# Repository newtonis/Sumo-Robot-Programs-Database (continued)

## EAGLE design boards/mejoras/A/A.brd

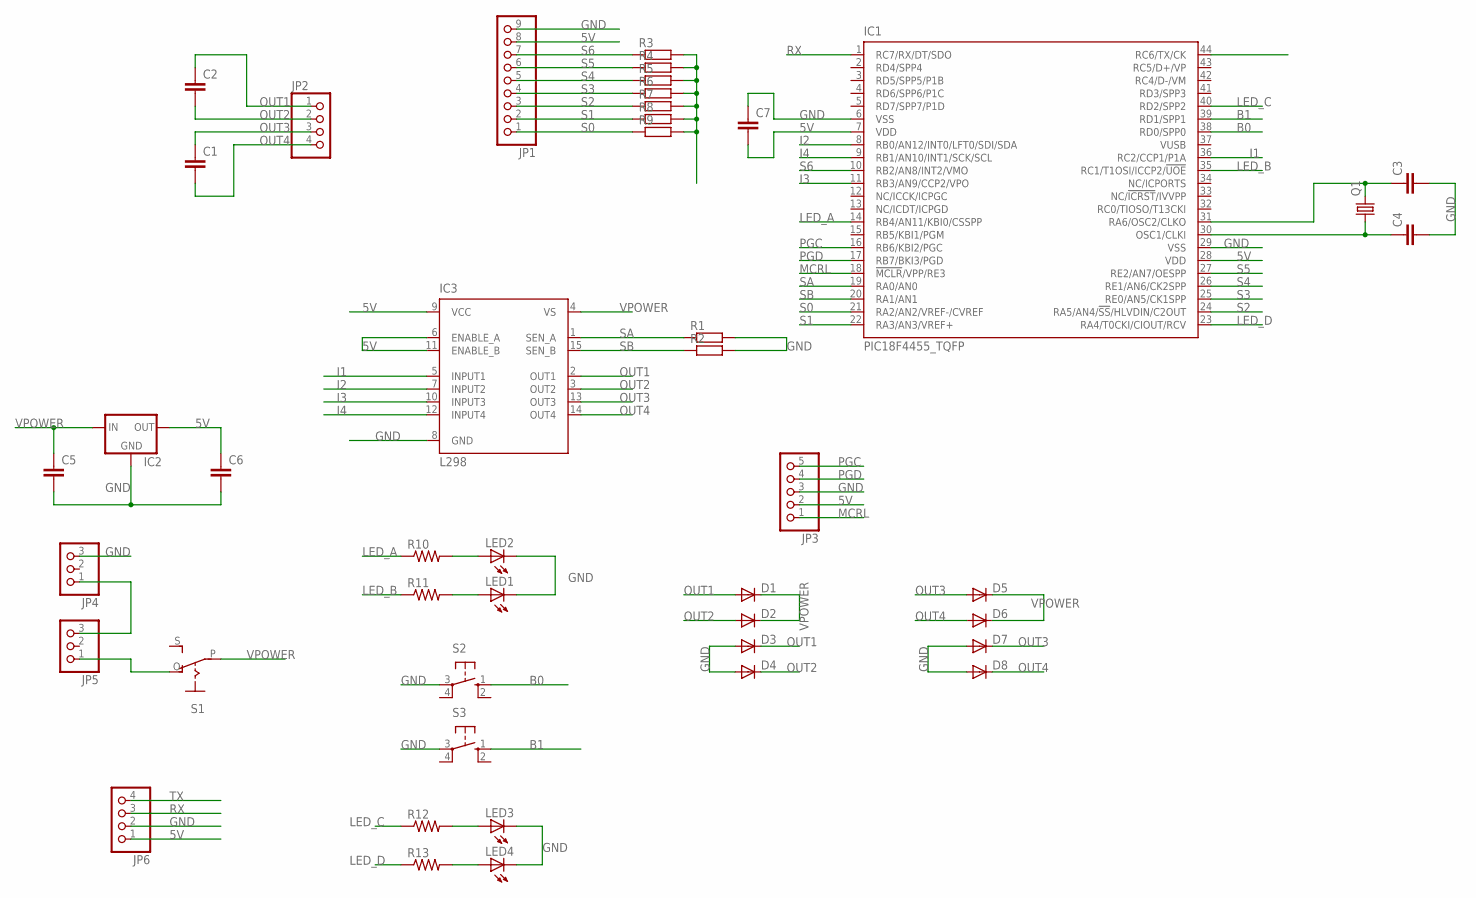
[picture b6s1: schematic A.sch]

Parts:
C1, C2, C3, C4, C5, C6, C7: C2,5-3; C2.5-3
D1, D2, D3, D4, D5, D6, D7, D8: DIODE-DO214AC; DO214AC
IC1: PIC18F4455_TQFP; TQFP44
IC2: 78XXS
IC3: L298; MULTIWATT-15
JP1: PINHD-1X9; 1X09
JP2, JP6: PINHD-1X4; 1X04
JP3: PINHD-1X5; 1X05
JP4, JP5: PINHD-1X3; 1X03
LED1, LED2, LED3, LED4: LEDCHIPLED_1206; CHIPLED_1206
Q1: CRYSTALHC49S; HC49/S
R1, R2: R-EU_R2512; R2512
R3, R4, R5, R6, R7, R8, R9: R-EU_M0805; M0805
R10, R11: R-US_M0805; M0805
R12, R13: R-US_R0805; R0805
S1: EG1218S; EG1218
S2, S3: 10-XX; B3F-10XX

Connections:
5V: C6.1, C7.2, IC1.7 (VDD), IC1.28 (VDD), IC2.OUT, IC3.6 (ENABLE_A), IC3.9 (VCC), IC3.11 (ENABLE_B), JP1.8, JP3.2, JP6.1, R3.2, R4.2, R5.2, R6.2, R7.2, R8.2, R9.2
B0: IC1.38 (RD0/SPP0), S2.1 (S)
B1: IC1.39 (RD1/SPP1), S3.1 (S)
GND: C3.2, C4.2, C5.2, C6.2, C7.1, D3.A, D4.A, D7.A, D8.A, IC1.6 (VSS), IC1.29 (VSS), IC2.GND, IC3.8 (GND), JP1.9, JP3.3, JP4.3, JP6.2, LED1.C, LED2.C, LED3.C, LED4.C, R1.2, R2.2, S2.3, S3.3
I1: IC1.36 (RC2/CCP1/P1A), IC3.5 (INPUT1)
I2: IC1.8 (RB0/AN12/INT0/LFT0/SDI/SDA), IC3.7 (INPUT2)
I3: IC1.11 (RB3/AN9/CCP2/VPO), IC3.10 (INPUT3)
I4: IC1.9 (RB1/AN10/INT1/SCK/SCL), IC3.12 (INPUT4)
LED_A: IC1.14 (RB4/AN11/KBI0/CSSPP), R10.1
LED_B: IC1.35 (RC1/T1OSI/ICCP2/!UOE), R11.1
LED_C: IC1.40 (RD2/SPP2), R12.1
LED_D: IC1.23 (RA4/T0CKI/CIOUT/RCV), R13.1
MCRL: IC1.18 (!MCLR!/VPP/RE3), JP3.1
unnamed: C4.1, IC1.30 (OSC1/CLKI), Q1.1
unnamed: C3.1, IC1.31 (RA6/OSC2/CLKO), Q1.2
unnamed: JP4.1, JP5.3
unnamed: LED2.A, R10.2
unnamed: LED1.A, R11.2
unnamed: LED3.A, R12.2
unnamed: LED4.A, R13.2
OUT1: C2.1, D1.A, D3.C, IC3.2 (OUT1), JP2.1
OUT2: C2.2, D2.A, D4.C, IC3.3 (OUT2), JP2.2
OUT3: C1.1, D5.A, D7.C, IC3.13 (OUT3), JP2.3
OUT4: C1.2, D6.A, D8.C, IC3.14 (OUT4), JP2.4
PGC: IC1.16 (RB6/KBI2/PGC), JP3.5
PGD: IC1.17 (RB7/BKI3/PGD), JP3.4
RX: IC1.1 (RC7/RX/DT/SDO), JP6.3
S0: IC1.21 (RA2/AN2/VREF-/CVREF), JP1.1, R9.1
S1: IC1.22 (RA3/AN3/VREF+), JP1.2, R8.1
S2: IC1.24 (RA5/AN4/!SS!/HLVDIN/C2OUT), JP1.3, R7.1
S3: IC1.25 (RE0/AN5/CK1SPP), JP1.4, R6.1
S4: IC1.26 (RE1/AN6/CK2SPP), JP1.5, R5.1
S5: IC1.27 (RE2/AN7/OESPP), JP1.6, R4.1
S6: IC1.10 (RB2/AN8/INT2/VMO), JP1.7, R3.1
SA: IC1.19 (RA0/AN0), IC3.1 (SEN_A), R1.1
SB: IC1.20 (RA1/AN1), IC3.15 (SEN_B), R2.1
TX: IC1.44 (RC6/TX/CK), JP6.4
VPOWER: C5.1, D1.C, D2.C, D5.C, D6.C, IC2.IN, IC3.4 (VS), S1.P
VPREV: JP5.1, S1.O

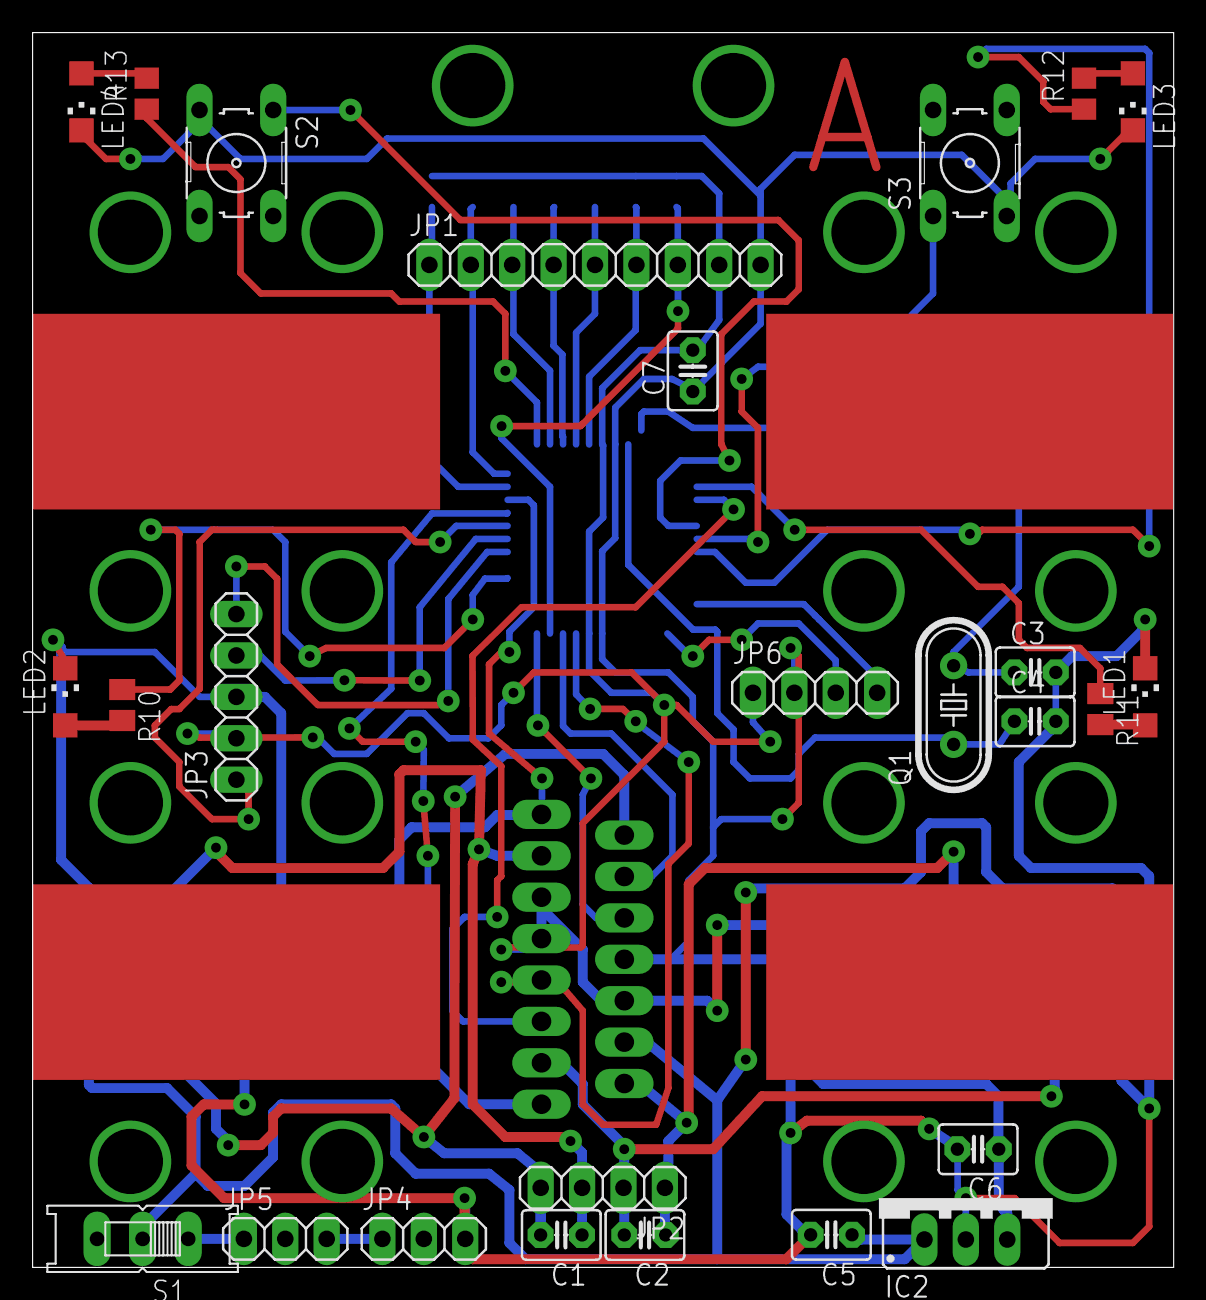
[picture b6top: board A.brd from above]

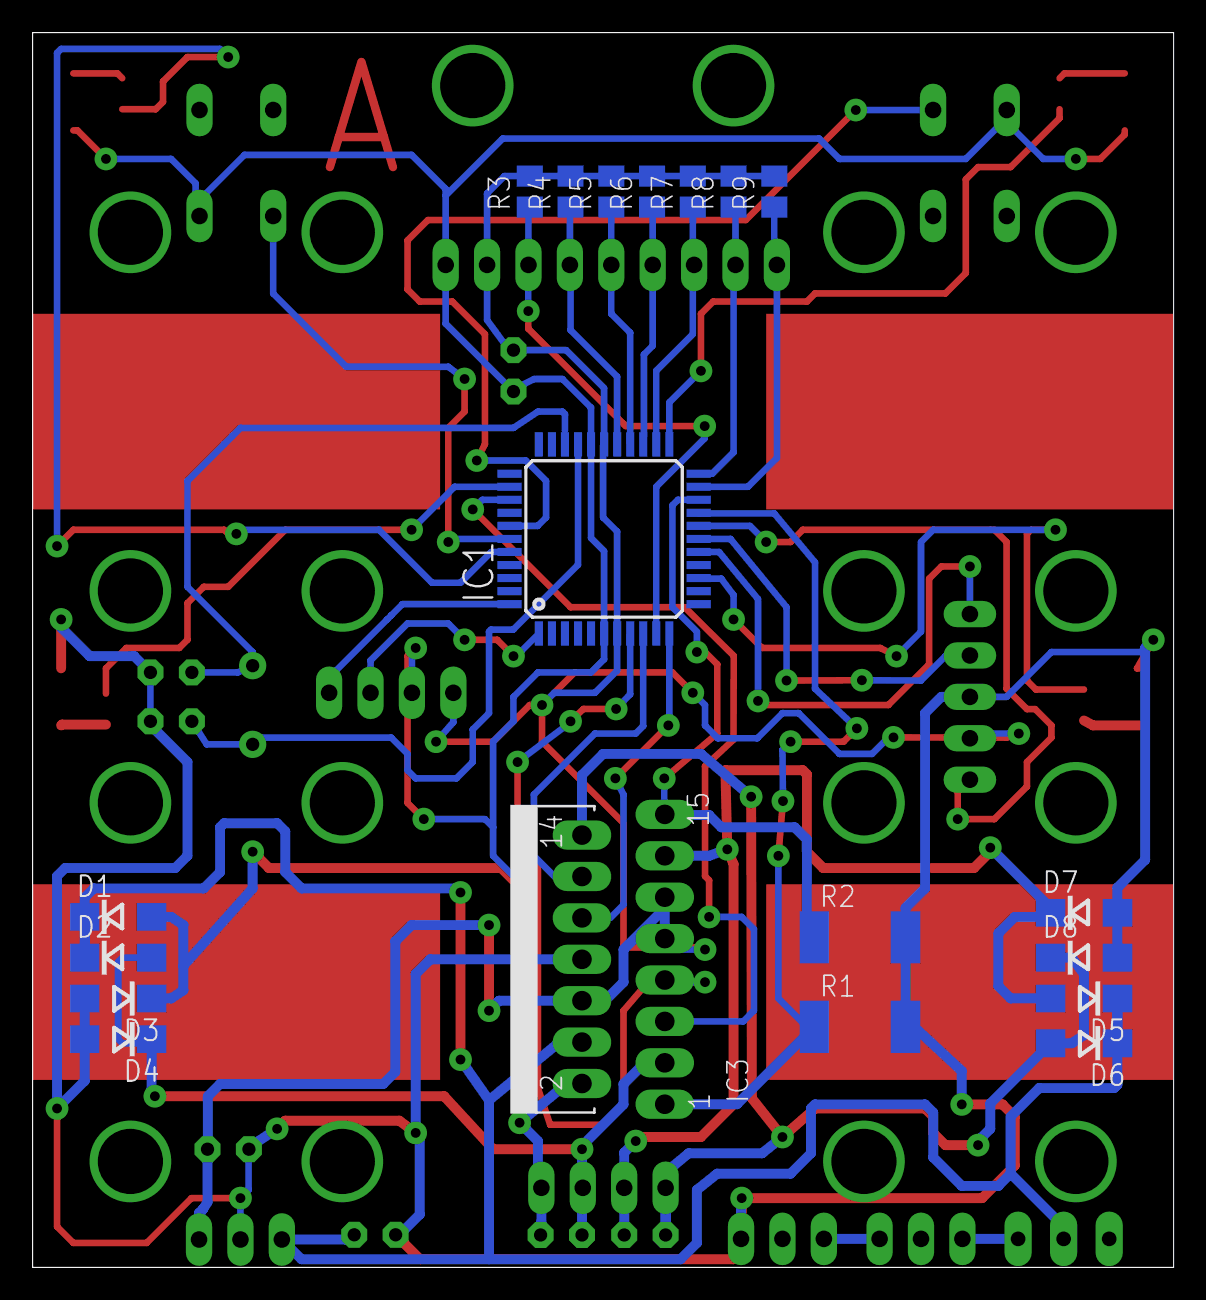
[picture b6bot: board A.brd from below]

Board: 2 copper layers, 70.0 x 75.8 mm, 45 parts (19 on the bottom side), 39 nets.

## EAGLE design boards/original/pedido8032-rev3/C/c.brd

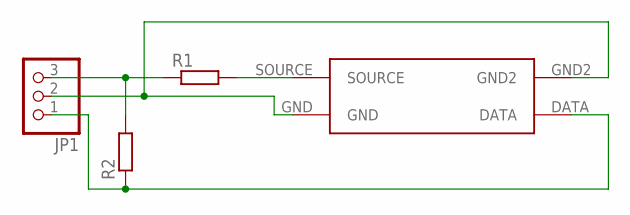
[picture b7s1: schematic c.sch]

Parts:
JP1: PINHD-1X3; 1X03
R1, R2: R-EU_M1206; M1206
U$1: GP2S24

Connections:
unnamed: JP1.3, R1.1, R2.2
unnamed: R1.2, U$1.SOURCE
unnamed: JP1.2, U$1.GND, U$1.GND2
unnamed: JP1.1, R2.1, U$1.DATA

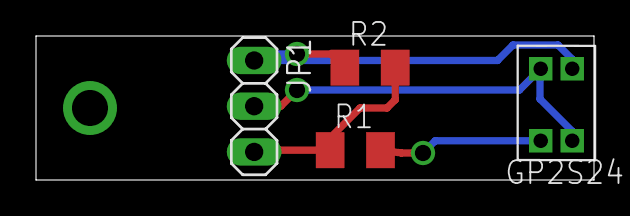
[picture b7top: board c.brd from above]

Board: 2 copper layers, 31.0 x 8.0 mm, 4 parts (0 on the bottom side), 4 nets.

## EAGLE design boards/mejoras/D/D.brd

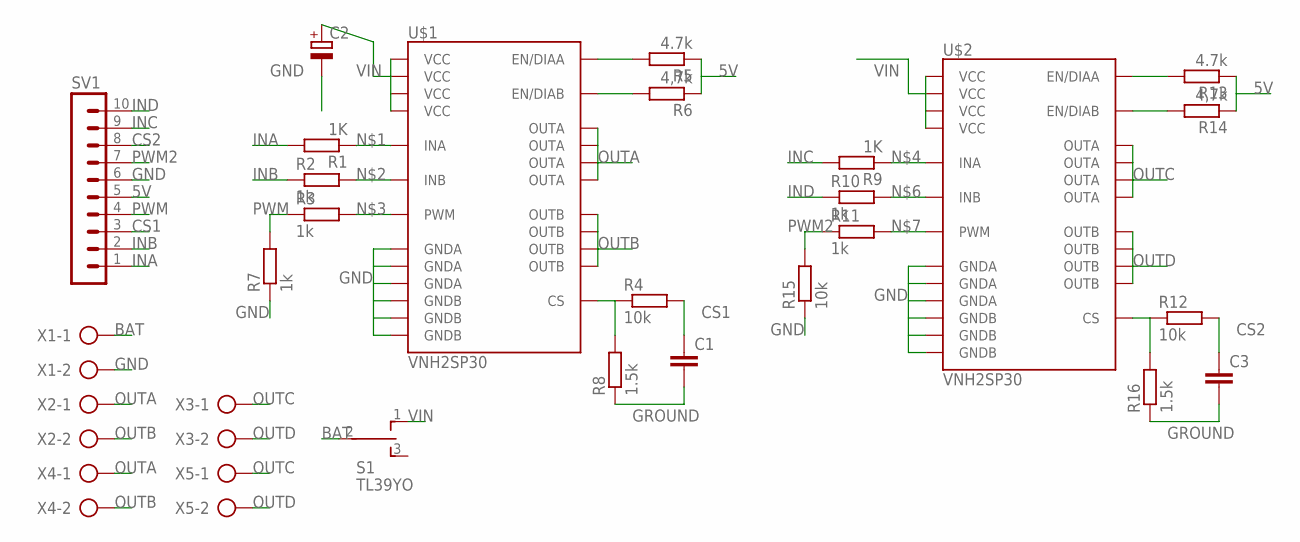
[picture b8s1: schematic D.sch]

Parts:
C1, C3: CAP1206; 1206
C2: CPOL-EUE3.5-8; E3,5-8
R1, R9: 1K; M1206
R2, R3, R7, R10, R11: 1k; M1206
R4, R12, R15: 10k; M1206
R5, R13: 4.7k; M1206
R6, R14: 4,7k; M1206
R8, R16: 1.5k; M1206
S1: TL39YO; TL3XYO
SV1: MA10-1W
U$1, U$2: VNH2SP30
X1, X2, X3, X4, X5: AK300/2

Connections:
5V: R5.1, R6.1, R13.1, R14.1, SV1.5
BAT: S1.2, X1.1
CS1: C1.1, R4.2, SV1.3
CS2: C3.1, R12.2, SV1.8
GND: C2.-, R7.1, R15.1, SV1.6, U$1.18 (GNDB), U$1.19 (GNDB), U$1.20 (GNDB), U$1.26 (GNDA), U$1.27 (GNDA), U$1.28 (GNDA), U$2.18 (GNDB), U$2.19 (GNDB), U$2.20 (GNDB), U$2.26 (GNDA), U$2.27 (GNDA), U$2.28 (GNDA), X1.2
GROUND: C1.2, C3.2, R8.1, R16.1
HJ: R12.1, R16.2, U$2.9 (CS)
INA: R1.2, SV1.1
INB: R2.1, SV1.2
INC: R9.2, SV1.9
IND: R10.1, SV1.10
unnamed: R1.1, U$1.5 (INA)
unnamed: R2.2, U$1.11 (INB)
unnamed: R3.2, U$1.8 (PWM)
unnamed: R9.1, U$2.5 (INA)
unnamed: R10.2, U$2.11 (INB)
unnamed: R11.2, U$2.8 (PWM)
unnamed: R4.1, R8.2, U$1.9 (CS)
unnamed: R5.2, U$1.6 (EN/DIAA)
unnamed: R6.2, U$1.10 (EN/DIAB)
unnamed: R13.2, U$2.6 (EN/DIAA)
unnamed: R14.2, U$2.10 (EN/DIAB)
OUTA: U$1.1 (OUTA), U$1.25 (OUTA), U$1.30 (OUTA), U$1.SLUG3 (OUTA), X2.1, X4.1
OUTB: U$1.15 (OUTB), U$1.16 (OUTB), U$1.21 (OUTB), U$1.SLUG2 (OUTB), X2.2, X4.2
OUTC: U$2.1 (OUTA), U$2.25 (OUTA), U$2.30 (OUTA), U$2.SLUG3 (OUTA), X3.1, X5.1
OUTD: U$2.15 (OUTB), U$2.16 (OUTB), U$2.21 (OUTB), U$2.SLUG2 (OUTB), X3.2, X5.2
PWM: R3.1, R7.2, SV1.4
PWM2: R11.1, R15.2, SV1.7
VIN: C2.+, S1.1 (O), U$1.3 (VCC), U$1.13 (VCC), U$1.23 (VCC), U$1.SLUG1 (VCC), U$2.3 (VCC), U$2.13 (VCC), U$2.23 (VCC), U$2.SLUG1 (VCC)

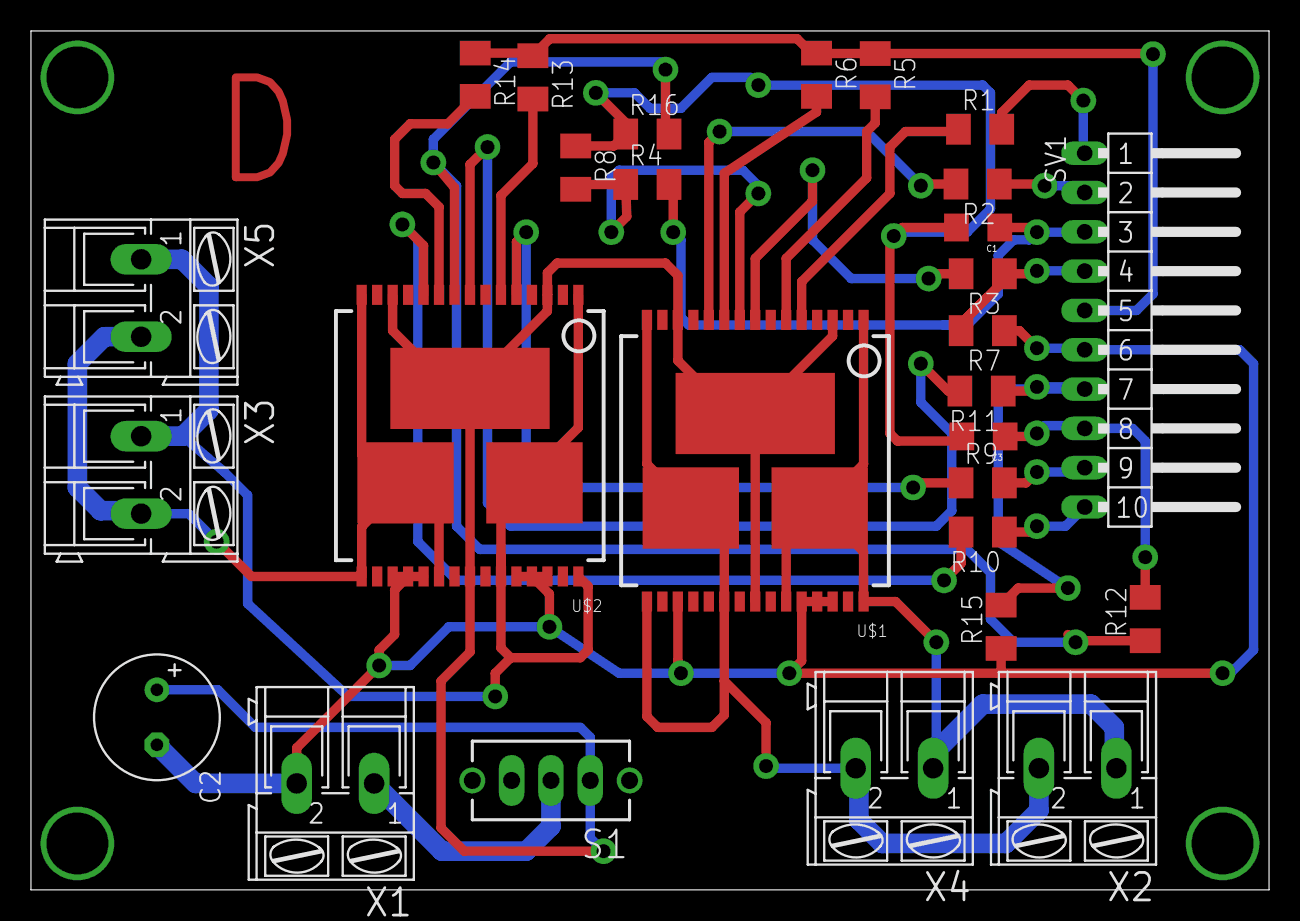
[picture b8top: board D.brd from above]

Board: 2 copper layers, 80.0 x 55.5 mm, 28 parts (0 on the bottom side), 29 nets.

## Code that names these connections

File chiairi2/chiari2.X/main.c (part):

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#pragma config PLLDIV = 5               // Internal Oscillator engaged 
#pragma config MCLRE  = OFF
#pragma config WDTPS  = 32768
#pragma config CCP2MX = OFF // Set PWM2 on Pin RB3
#pragma config PBADEN = OFF
#pragma config CPUDIV = OSC1_PLL2 /// Divide 96 MHz PLL frequency by 2 => Fosc=48Mhz
#pragma config USBDIV = 2
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#pragma config EBTRB  = OFF

// Input Output
#define LED_1 PORTBbits.RB0
#define LED_2 PORTBbits.RB1
#define LED_3 PORTBbits.RB2
#define LED_4 PORTBbits.RB4
#define LED_5 PORTBbits.RB5

// Buttons
#define BUTTON_1 PORTDbits.RD2
#define BUTTON_2 PORTDbits.RD3

// Motors
#define M2_B PORTDbits.RD1 // Invert motor pins (as pwm pins are inverted)
#define M2_A PORTDbits.RD0
#define M1_B PORTCbits.RC1
#define M1_A PORTCbits.RC0

// Sensors
#define S1 PORTDbits.RD7
#define S2 PORTDbits.RD6
#define S3 PORTDbits.RD5
#define S4 PORTDbits.RD4
#define S5 PORTCbits.RC5

// 5 available general propouse counters
long long int counter[5]; 
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    // Interal oscillator default 8 MHZ
    OSCCONbits.IRCF = 7;
    
    // Desactivo comparadores para poder usar los pines RA0:RA3
    CMCON=0x07;
    
    // Disable USB
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    // Wixel (for debug)
    
    // Start tris value for wixel ports
    TRISCbits.RC6 = 1;
    TRISCbits.RC7 = 1;
    
    BAUDCONbits.RXDTP=0; //Asynchronous mode: 1 = RX data is inverted 0 = RX data received is not inverted
    BAUDCONbits.TXCKP=0; //XCKP: Clock and Data Polarity Select bit Asynchronous mode: 1 = TX data is inverted 0 = TX
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    // Input Output
    
    // Leds
    TRISBbits.RB0 = 0;
    TRISBbits.RB1 = 0;
    TRISBbits.RB2 = 0;
    TRISBbits.RB4 = 0;
    TRISBbits.RB5 = 0;
    
    // Buttons
    TRISDbits.RD2 = 1;
    TRISDbits.RD3 = 1;
    
    // Analog inputs
    TRISAbits.RA0 = 1;
    TRISAbits.RA1 = 1;
    TRISAbits.RA2 = 1;
    TRISAbits.RA3 = 1;
    TRISAbits.RA4 = 1;
    TRISEbits.RE0 = 1;
    
    // Motors
    TRISDbits.RD1 = 0;
    TRISDbits.RD0 = 0;
    TRISCbits.RC1 = 0;
    TRISCbits.RC0 = 0;
    TRISBbits.RB3 = 0;
    TRISCbits.RC2 = 0;
    
    // Sensors
    TRISDbits.RD7 = 1;
    TRISDbits.RD6 = 1;
    TRISDbits.RD5 = 1;
    TRISDbits.RD4 = 1;
    //TRISCbits.RC5 = 1; // Auto input
}

// Analog read
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
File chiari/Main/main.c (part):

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#define SPECIAL 1 ///We will program the fall down area

/*** SETTING STANDARD I/O NAMES FOR EACH PORT ***/
/*#define L_RED PORTDbits.RD4
#define L_YELLOW PORTDbits.RD5
#define L_GREEN PORTDbits.RD6

#define B_RED PORTDbits.RD0
#define B_YELLOW PORTDbits.RD1
#define B_GREEN PORTDbits.RD2*/
#define LED_0 PORTDbits.RD1
#define LED_1 PORTDbits.RD2
#define LED_2 PORTDbits.RD3

#define BTN PORTCbits.RC4


/*#define BSP PORTCbits.RC2
#define ADIR PORTBbits.RB2

#define ASP PORTDbits.RD3
#define BDIR PORTBbits.RB0*/
#define ADIR PORTDbits.RD0
#define BDIR PORTCbits.RC0

/*#define V0 PORTEbits.RE2
#define V1 PORTEbits.RE1
#define V2 PORTEbits.RE0
#define V3 PORTAbits.RA5
#define V4 PORTAbits.RA4*/
#define PCLK PORTAbits.RA4
#define P0 PORTAbits.RA3
#define P1 PORTAbits.RA2
#define P2 PORTBbits.RB5
#define P3 PORTBbits.RB4


//* para blanco negro */
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        //LED_1 = 1;
        //LED_1 = TIME % 6000 > 3000;
        //MotorUpdate();
        //PORTDbits.RD1 = 1;
        LED_1 = SS[0];
        if (PCLK == 0){
            SS[0] = P0;
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
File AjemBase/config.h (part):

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
//	DISPLAY 7 SEGMENTOS y BUZZER
#ifdef D7SEG_INVERSO
	#define PIN_LED_A		LB2
	#define TRIS_LED_A		TRISB2
	#define PIN_LED_B		LB0
	#define TRIS_LED_B		TRISB0
	#define PIN_LED_C		LB6
	#define TRIS_LED_C		TRISB6
	#define PIN_LED_D		LB5
	#define TRIS_LED_D		TRISB5
	#define PIN_LED_E		LB4
	#define TRIS_LED_E		TRISB4
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	#define PIN_LED_DP		LB7
	#define TRIS_LED_DP		TRISB7
#else
	#define PIN_LED_A		LB5
	#define TRIS_LED_A		TRISB5
	#define PIN_LED_B		LB4
	#define TRIS_LED_B		TRISB4
	#define PIN_LED_C		LB3
	#define TRIS_LED_C		TRISB3
	#define PIN_LED_D		LB2
	#define TRIS_LED_D		TRISB2
	#define PIN_LED_E		LB0
	#define TRIS_LED_E		TRISB0
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	#define TRIS_LED_DP		TRISB1
#endif

#define PIN_BUZZER		PORTAbits.RA4
#define TRIS_BUZZER		TRISA4

//	PULSADORES
#define PIN_SW1			PORTAbits.RA0
#define TRIS_SW1		TRISA0
#define PIN_SW2			PORTAbits.RA2
#define TRIS_SW2		TRISA2
#define PIN_SW3			PORTAbits.RA1
#define TRIS_SW3		TRISA1

//	SENSORES
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#define PIN_ULTRA_T4	LATD2
#define TRIS_ULTRA_T4	TRISD2

#define PIN_ULTRA_E1	PORTDbits.RD5
#define TRIS_ULTRA_E1	TRISD5
#define PIN_ULTRA_E2	PORTDbits.RD4
#define TRIS_ULTRA_E2	TRISD4
#define PIN_ULTRA_E3	PORTCbits.RC5
//#define TRIS_ULTRA_E3	TRISC5
#define PIN_ULTRA_E4	PORTCbits.RC4
//#define TRIS_ULTRA_E4	TRISC4

#define PIN_LINEA1		PORTEbits.RE1
#define TRIS_LINEA1		TRISE1
#define PIN_LINEA2		PORTEbits.RE0
#define TRIS_LINEA2		TRISE0
#define PIN_LINEA3		PORTAbits.RA5
#define TRIS_LINEA3		TRISA5
#define PIN_LINEA4		PORTEbits.RE2
#define TRIS_LINEA4		TRISE2

//	MOTORES
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//	SERIAL
#define PIN_TX			LATC6
#define TRIS_RX			TRISC7
#define PIN_RX			PORTCbits.RC7
#define TRIS_TX			TRISC6


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
/** MACROS **/
#define setGPIO(output, value)									\
		(output == (LED_A)			?	PIN_LED_A = (value)		\
		:(output == (LED_B)			?	PIN_LED_B = (value)		\
		:(output == (LED_C)			?	PIN_LED_C = (value)		\
		:(output == (LED_D)			?	PIN_LED_D = (value)		\
		:(output == (LED_E)			?	PIN_LED_E = (value)		\
		:(output == (LED_F)			?	PIN_LED_F = (value)		\
		:(output == (LED_G)			?	PIN_LED_G = (value)		\
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
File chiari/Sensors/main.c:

/* 
 * File:   main.c
 * Author: newtonis
 *
 * Created on August 16, 2014, 11:51 AM
 */

 //http://www.92gag.com/top-rated/easy-make-i-love-you-895

#include <xc.h>

#pragma config BOREN = OFF, CPD = OFF, FOSC = INTOSCIO, MCLRE = OFF, WDTE = OFF, CP = OFF, LVP = OFF, PWRTE = OFF
#define _XTAL_FREQ 4000000

#define INICIO  0
#define PAUSA   1
#define LEER    2
#define APAGADO 3

#define OUTPUT 0
#define INPUT  1

#define or ||
#define and &&
#define not !

#define IN_IR0 PORTBbits.RB2
#define IN_IR1 PORTBbits.RB1
#define IN_IR2 PORTBbits.RB0
#define IN_IR3 PORTAbits.RA4
#define IN_IR4 PORTAbits.RA3
#define IN_IR5 PORTAbits.RA2
#define IN_IR6 PORTAbits.RA1

#define OUT_PCLK PORTBbits.RB4
#define OUT_IR0 PORTBbits.RB5
#define OUT_IR1 PORTAbits.RA6
#define OUT_IR2 PORTAbits.RA7
#define OUT_IR3 PORTAbits.RA0

//#define IN_DIS PORTAbits.RA0

#define CVALORES 8

#define CERCA 0x04
#define LEJOS 0x10

long long times;
char estado;
char contador;
char ciclos;
int t = 0;

char sensor[CVALORES];
char V[CVALORES];


char valores[CVALORES] = {1,2,6,8,12};
char actual;
char st;

void init(void);
void configurar_pwm(void);
void configurar_IO(void);
void configurar_timer0(void);
void configurar_timer1(void);
void sensores(void);
void read();
void actualizar_salidas(void);
void DUTYSet(int value);
void store(){
    int i;
    V[0] = V[0] or (not IN_IR0);
    V[1] = V[1] or (not IN_IR1);
    V[2] = V[2] or (not IN_IR2);
    V[3] = V[3] or (not IN_IR3);
    V[4] = V[4] or (not IN_IR4);
    V[5] = V[5] or (not IN_IR5);
    V[6] = V[6] or (not IN_IR6);
    st = 0;// flag set to update
}
void set(){
    if (st == 0){
        if (t == 0){
            OUT_PCLK = 0;
            OUT_IR0 = V[0];
            OUT_IR1 = V[1];
            OUT_IR2 = V[2];
            OUT_IR3 = V[3]; 
            t = 1;
        }else{
            OUT_PCLK = 1;
            OUT_IR0 = V[0];
            OUT_IR1 = V[1];
            OUT_IR2 = V[2];
            OUT_IR3 = V[3];
            t = 0;
        }
        int j;
        for (j = 0;j < CVALORES;j++) V[j] = 0;
        st = 1;
    }
}
int main(int argc, char** argv) {
    st = 1;
    times = 0;
    init();
    configurar_IO();
    configurar_pwm();
    set();
    /*configurar_timer1();
    configurar_timer0();*/
    TMR2IE=1;
    PEIE=1;
    GIE=1;
    while (1){
        if (times > 540 && times < 560){
            store();
        }else{
            set();
        }
    }
}

void interrupt ISR(){
    if(TMR2IE && TMR2IF){
        //TMR2 overflow
        times++;
        if(times == 504){
            TRISB3 = 0;
        }
        if(times == 560){
            TRISB3 = 1;
            times = 0;
        }
        TMR2IF= 0;
    }
}
void init(void){
    CMCON = 0x07;
    contador = 0;
    estado = INICIO;
    ciclos = 0;
    actual = 0;
    
    ///// 0000
}
void SetDuty(int S){
    // v goes from 0 to 100
    //now goes from 0 to 78 
    CCP1CONbits.CCP1X = (S % 4) > 1;
    CCP1CONbits.CCP1Y = (S % 4) % 2;
    CCPR1L = S / 4;
}
void configurar_pwm(void){
    T2CONbits.TMR2ON=1; // timer2 prendido
    T2CONbits.TOUTPS=0; // hasta 15
    T2CONbits.T2CKPS=0; // 00=1:1 01=1:4 1x=1:16

    TRISBbits.TRISB3=0; // pwm salida
    PR2=26;//17;//26; // periodo 30Khz

    // MENOR VALOR A MAYOR VALOR
    // 78 -> 100 %
    /// 72 is the max cycle to send
    //SetDuty(7);
    CCP1CON = 12; // 12
   // CCPR1L = 0x02;
    //CCPR1L=0; //apagado
    //CCP1CON=12;
    SetDuty(15);
}
void configurar_timer1(void){
    TMR1H=0xFC;
    TMR1L=0x18;

    PIE1bits.TMR1IE     = 0; //desabilita interrupcion
    PIR1bits.TMR1IF     = 0; //desborde

    T1CONbits.T1CKPS    = 0; //prescaler

    T1CONbits.nT1SYNC   = 1;
    T1CONbits.T1OSCEN   = 0;
    T1CONbits.TMR1CS    = 0;
    T1CONbits.TMR1ON    = 0; //on-off
    T1CONbits.TMR1ON    = 1; //prender timer
}
void configurar_timer0(void){
    OPTION_REGbits.T0CS = 0;
    OPTION_REGbits.PSA  = 0;
    OPTION_REGbits.PS   = 1;

    INTCONbits.T0IF     = 0;
    INTCONbits.T0IE     = 1;
    INTCONbits.GIE      = 1;
}
void configurar_IO(void){
    TRISB3 = OUTPUT;  //pwm
   
    TRISB2 = INPUT;
    TRISB1 = INPUT;
    TRISB0 = INPUT;
    TRISA4 = INPUT;
    TRISA3 = INPUT;
    TRISA2 = INPUT;
    TRISA1 = INPUT;

    TRISB4 = OUTPUT;
    TRISB5 = OUTPUT;
    TRISA6 = OUTPUT;
    TRISA7 = OUTPUT;
    TRISA0 = OUTPUT;
}
/*void interrupt t0_int(void){
    INTCONbits.T0IF=0;
    contador ++;
}*/
/*void interrupt t2_int(void){
    if (PIR1bits.TMR2IF){
        PIR1bits.TMR2IF=0;
        times ++;
    }
}*/
void OnTIMER2(){
    T2CONbits.TMR2ON=1; // timer2 prendido
    T2CONbits.TOUTPS=0; // hasta 15
    T2CONbits.T2CKPS=0; // 00=1:1 01=1:4 1x=1:16
    TRISBbits.TRISB3=0; // pwm salida
}
void sensores(){
    switch (estado){
        case INICIO:
            //CCPR1L = 0x01; //IN_DIS ? CERCA : LEJOS;
            //CCPR1L= valores[actual]; //prender pwm
            //OnTIMER2();
            TRISB3 = OUTPUT;
            estado = PAUSA;
            times = 0;
        break;
        case PAUSA:
            if(times > 100){  //desborde timer 2
                //PIR1bits.TMR1IF=0; //borro desborde
                //T1CONbits.TMR1ON=0; //apagar timer
                //TMR1H=0xFC;
                //TMR1L=0x17;
                read();
                TRISB3 = INPUT;
                //CCPR1L=0; //apagado pwm
                estado = APAGADO;
                times = 0;
            }
        break;
        case APAGADO:
            if(times > 100){  //desborde timer 2
                estado = INICIO;
            }
        break;
    }
}
void read(){
    /*OUT_IR0 = not IN_IR0;
    OUT_IR1 = not IN_IR1;
    OUT_IR2 = not IN_IR2;
    OUT_IR3 = not IN_IR3;
    OUT_IR4 = not IN_IR4;*/
}
void DUTYSet(int value){
    CCPR1L = value / 4;
    CCP1CON = value % 4;
}

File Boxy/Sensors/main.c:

/* 
 * File:   main.c
 * Author: newtonis
 *
 * Created on August 16, 2014, 11:51 AM
 */

#include <xc.h>

#pragma config BOREN = OFF, CPD = OFF, FOSC = INTOSCIO, MCLRE = OFF, WDTE = OFF, CP = OFF, LVP = OFF, PWRTE = OFF
#define _XTAL_FREQ 4000000

#define INICIO  0
#define PAUSA   1
#define LEER    2
#define APAGADO 3

#define OUTPUT 0
#define INPUT  1

#define IN_IR0 PORTAbits.RA0
#define IN_IR1 PORTAbits.RA1
#define IN_IR2 PORTAbits.RA2
#define IN_IR3 PORTAbits.RA3
#define IN_IR4 PORTAbits.RA4

#define OUT_IR0 PORTBbits.RB0
#define OUT_IR1 PORTBbits.RB4
#define OUT_IR2 PORTBbits.RB5
#define OUT_IR3 PORTBbits.RB6
#define OUT_IR4 PORTBbits.RB7

#define or ||
#define and &&
#define not !

#define IN_DIS PORTAbits.RA0

#define CVALORES 5

#define CERCA 0x04
#define LEJOS 0x10

char estado;
char contador;
char ciclos;

char sensor[CVALORES];
char V[CVALORES];

long long times;
char valores[CVALORES] = {1,2,6,8,12};
char actual;
int cnt = 0;
char st;

void init(void);
void configurar_pwm(void);
void configurar_IO(void);
void configurar_timer0(void);
void configurar_timer1(void);
void sensores(void);
void read();
void actualizar_salidas(void);
void DUTYSet(int value);

void SetDuty(int S){
    // v goes from 0 to 100
    //now goes from 0 to 78 
    CCP1CONbits.CCP1X = (S % 4) > 1;
    CCP1CONbits.CCP1Y = (S % 4) % 2;
    CCPR1L = S / 4;
}

void store(){
    int i;
    V[0] = V[0] or (not IN_IR0);
    V[1] = V[1] or (not IN_IR1);
    V[2] = V[2] or (not IN_IR2);
    V[3] = V[3] or (not IN_IR3);
    V[4] = V[4] or (not IN_IR4);
    st = 0;// flag set to update
}
void set(){
    if (st == 0){
        OUT_IR0 = V[0];
        OUT_IR1 = V[1];
        OUT_IR2 = V[2];
        OUT_IR3 = V[3];
        OUT_IR4 = V[4];
        int j;
        for (j = 0;j < CVALORES;j++) V[j] = 0;
        st = 1;
    }
}

#define INTENSITY 15

int main(int argc, char** argv) {
    st = 1;
    times = 0;
    init();
    configurar_IO();
    configurar_pwm();
    set();
    TMR2IE=1;
    PEIE=1;
    GIE=1;
    
    //onfigurar_timer1();
    //configurar_timer0();
    while (1){
        if (times > 540 && times < 560){
            store();
        }else{
            set();
        }
        /*OUT_IR0 = 1;
        OUT_IR1 = 0;
        OUT_IR2 = 0;
        OUT_IR3 = 0;
        OUT_IR4 = 0;*/
        //sensores();
    }
}

void interrupt ISR(){
    if(TMR2IE && TMR2IF){
        //TMR2 overflow
        times++;
        if(times == 504){
            TRISB3 = 0;
        }
        if(times == 560){
            TRISB3 = 1;
            times = 0;
        }
        TMR2IF= 0;
    }
}

void init(void){
    CMCON = 0x07;
    contador = 0;
    estado = INICIO;
    ciclos = 0;
    actual = 0;
    //CCPR1L = 0x01; //IN_DIS ? CERCA : LEJOS;
    //CCPR1H = 0x00; // valores[actual]; //prender pwm

    ///// 0000
}
void configurar_pwm(void){
    T2CONbits.TMR2ON=1; // timer2 prendido
    T2CONbits.TOUTPS=0; // hasta 15
    T2CONbits.T2CKPS=0; // 00=1:1 01=1:4 1x=1:16
    TRISBbits.TRISB3=0; // pwm salida
    PR2=17;//26; // periodo 30Khz
    //CCPR1L=0x01; //apagado
    CCP1CON=12;

    SetDuty( INTENSITY );
}
void configurar_timer1(void){
    TMR1H=0xFC;
    TMR1L=0x18;

    PIE1bits.TMR1IE     = 0; //desabilita interrupcion
    PIR1bits.TMR1IF     = 0; //desborde

    T1CONbits.T1CKPS    = 0; //prescaler

    T1CONbits.nT1SYNC   = 1;
    T1CONbits.T1OSCEN   = 0;
    T1CONbits.TMR1CS    = 0;
    T1CONbits.TMR1ON    = 0; //on-off
    T1CONbits.TMR1ON    = 1; //prender timer
}
void configurar_timer0(void){
    OPTION_REGbits.T0CS = 0;
    OPTION_REGbits.PSA  = 0;
    OPTION_REGbits.PS   = 1;

    INTCONbits.T0IF     = 0;
    INTCONbits.T0IE     = 1;
    INTCONbits.GIE      = 1;
}
void configurar_IO(void){
    TRISB3 = OUTPUT;  //pwm
   
    TRISA0 = INPUT;
    TRISA1 = INPUT;
    TRISA2 = INPUT;
    TRISA3 = INPUT;
    TRISA4 = INPUT;
    
    TRISB0 = OUTPUT;
    TRISB4 = OUTPUT;
    TRISB5 = OUTPUT;
    TRISB6 = OUTPUT;
    TRISA7 = OUTPUT;
}
/*void interrupt t0_int(void){
    INTCONbits.T0IF=0;
    contador ++;
}*/
void sensores(){
    switch (estado){
        case INICIO:
           // CCPR1L = 0x01; //IN_DIS ? CERCA : LEJOS;
            //CCPR1H = 0x00; // valores[actual]; //prender pwm
            TRISB3 = OUTPUT;
            T1CONbits.TMR1ON=1; //prender timer
            estado = PAUSA;
            cnt = 0;
            contador = 0;
        break;
        case PAUSA:
            //cnt ++;
            //if (contador >= 2){
            if(PIR1bits.TMR1IF==1){  //desborde
                PIR1bits.TMR1IF=0; //borro desborde
                T1CONbits.TMR1ON=0; //apagar timer
                TMR1H=0xFC;
                TMR1L=0x17;
                estado = LEER;
            }
        break;
        case LEER:
            read();
            PIR1bits.TMR1IF=0; //borro desborde
            T1CONbits.TMR1ON=0; //apagar timer
            contador = 0;
            //CCPR1L=0; //apagado pwm
            TRISB3 = INPUT;
            estado = APAGADO;
            cnt = 0;
        break;
        case APAGADO:
            if(contador >= 10){
                estado = INICIO;
            }
        break;
    }
}
void read(){
    OUT_IR0 = IN_IR0;
    OUT_IR1 = IN_IR1;
    OUT_IR2 = IN_IR2;
    OUT_IR3 = IN_IR3;
    OUT_IR4 = IN_IR4;
}
void DUTYSet(int value){
    CCPR1L = value / 4;
    CCP1CON = value % 4;
}

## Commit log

2016-07-22 added initial files
2016-07-23 add 2
2016-07-27 added boxy
2016-07-31 7312
2016-07-31 test
2016-08-02 8021
2017-02-07 2-07-17
2017-02-08 2-08-17
2017-02-10 2-10-17
2017-05-23 add mark4
2017-08-07 8-07-1017
2017-08-19 8/18
2017-08-19 8/19
2024-07-27 added hex backup rayito
2024-07-28 Added too simple hex program
2024-07-28 Added rayito 3.2
2024-07-28 added eeprom functions for rayito 3.2@
2024-07-28 added eeprom functions for rayito 3.2, updated specific logic
2025-01-07 added circuits
2025-01-09 changes to g circuit
2025-01-12 corrected bug
2025-03-16 udpated new circuits
2025-04-11 added new sumo robot logic start board
2025-04-11 added eagle libs
2025-04-13 added board h first version
2025-04-17 added circuit H and I
2025-04-17 updated board h and i
2025-04-17 added on button
2025-04-19 small fixes to h
2025-04-19 small fixes to g and i
2025-04-25 new boards
2025-04-26 agregado diseño robot 3d chiari
2025-04-30 updated boards
2025-06-14 added chiari 2 program
2025-06-21 added first program for chiari
2025-06-28 updated program and add new tests
2025-07-08 added new buttons programs
2025-07-12 added new button logic
2025-07-16 added integration test variable testing
2025-07-16 added integrated motor test program final version
2025-07-31 fix pwm bug
2025-08-02 added test sensors and first menu
2025-08-03 small program adjustment
2025-08-06 finished program
2026-01-10 fixed main program
